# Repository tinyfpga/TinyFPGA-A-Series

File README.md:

# TinyFPGA-A-Series
The TinyFPGA A-Series boards are tiny bare-bones FPGA boards with a low cost per logic element.  They are programmed via their built-in JTAG interface and only contain the bare-minimum of components for the FPGA to function.  They measure 18mm x 30.5mm and fit well in breadboards.

## Features
The A-series boards use either XO2-256 or XO2-1200 FPGAs from Lattice.  It's a good idea to reference the [MachXO2 Family Data Sheet](http://www.latticesemi.com/~/media/LatticeSemi/Documents/DataSheets/MachXO23/MachXO2FamilyDataSheet.pdf?document_id=38834) for details.

### FPGA Feature Summary
|                  | TinyFPGA A1 | TinyFPGA A2 |
|------------------|:-----------:|:-----------:|
| FPGA Chip        |   XO2-256   |   XO2-1200  |
| Logic Cells      |     256     |     1200    |
| Distributed RAM  |   2 KBits   |   10 KBit   | 
| Block RAM        |             |   64 KBit   |
| User Flash       |             |   64 KBit   |
| Phase Lock Loops |             |      1      |
| User IO Pins     |     21      |     21      |

### Common Features
+ Small form-factor that is breadboard friendly; plenty of space on either side for connecting jumpers or components.
+ Easily accessible JTAG interface pins located both on the side IO connectors as well as a header on the top of the board.  This is an inexpensive way to support in circuit programming and testing.
+ Low-power and low-cost design relies on integrated FPGA functionality: internal configuration flash memory, internal clock generator, and fixed 3.3v power supply requirement.  External memory, clocks, and power supplies can be added external to the board.

## Building your own TinyFPGA A1 or A2 Boards
The TinyFPGA A-Series boards are possible to build in an adequately equipped home lab.  The resistors and capacitors are 0603 surface mount parts, and the FPGA is in a QFN32 package which can be soldered either by hand or with solder paste and a reflow oven.  It can be tricky to solder the QFN32 package by hand, but it is possible.  However it is much easier to use solder paste and a stencil along with a hot air-gun or reflow oven.  The following parts, supplies, and tools will help ensure a successful build:
+ Parts for the TinyFPGA [A1](https://octopart.com/bom-tool/Xj5vAWfE) or [A2](https://octopart.com/bom-tool/Cm0HpT6j)
+ [Lead-Free Solder Paste](https://www.amazon.com/gp/product/B00HKK6XHC)
+ [Stainless Steel Solder Paste Squeegee](http://dirtypcbs.com/store/details/14/solder-paste-squeegee)
+ [TinyFPGA A-Series Solder Paste Stencil](https://www.oshstencils.com)
  + You'll need to generate the gerber files and upload the solder paste layer.  Either stainless steel or polymide stencils should work.
+ [TinyFPGA A-Series PCBs](https://oshpark.com/shared_projects/2xu90fiY)
+ [Precision Tweezers](https://www.amazon.com/Precision-Anti-static-Marrywindix-Electronics-Jewelry-making/dp/B00DVIEJ14) for placing parts on the board
+ [Reflow Oven](http://www.whizoo.com/) or an [electric griddle](https://www.amazon.com/Presto-07211-Liddle-Griddle/dp/B00006IUWL)

## Buy TinyFPGA A1 or A2 Boards
If you don't want to go through the hassle of ordering parts, tools, and supplies and assembling the boards yourself you can order professionally assembled and tested boards from the [TinyFPGA Store](https://www.tindie.com/stores/tinyfpga/).  These boards are fabricated and assembled in a professional PCB fab that manufactures and assembles many other consumer, industrial and military electronics.  They go through an automated testing and programming process to ensure the board is healthy and ready to program over JTAG.

## Project Directory Structure
### board
This contains a [KiCad](http://kicad.org/) project with the schematic and layout of the B-series boards.  The board is designed with 4/4mil track size/spacing and 0.2mm hole size.

## License
The TinyFPGA A-Series project is an open source project licensed under GPLv3.  Please see the included LICENSE file for details.  If you do wish to distribute boards derived from this open source hardware project then you must also release the source files for the boards under GPLv3.  You are free to do this, but please improve upon the original design and provide a tangible benefit for users of the board.

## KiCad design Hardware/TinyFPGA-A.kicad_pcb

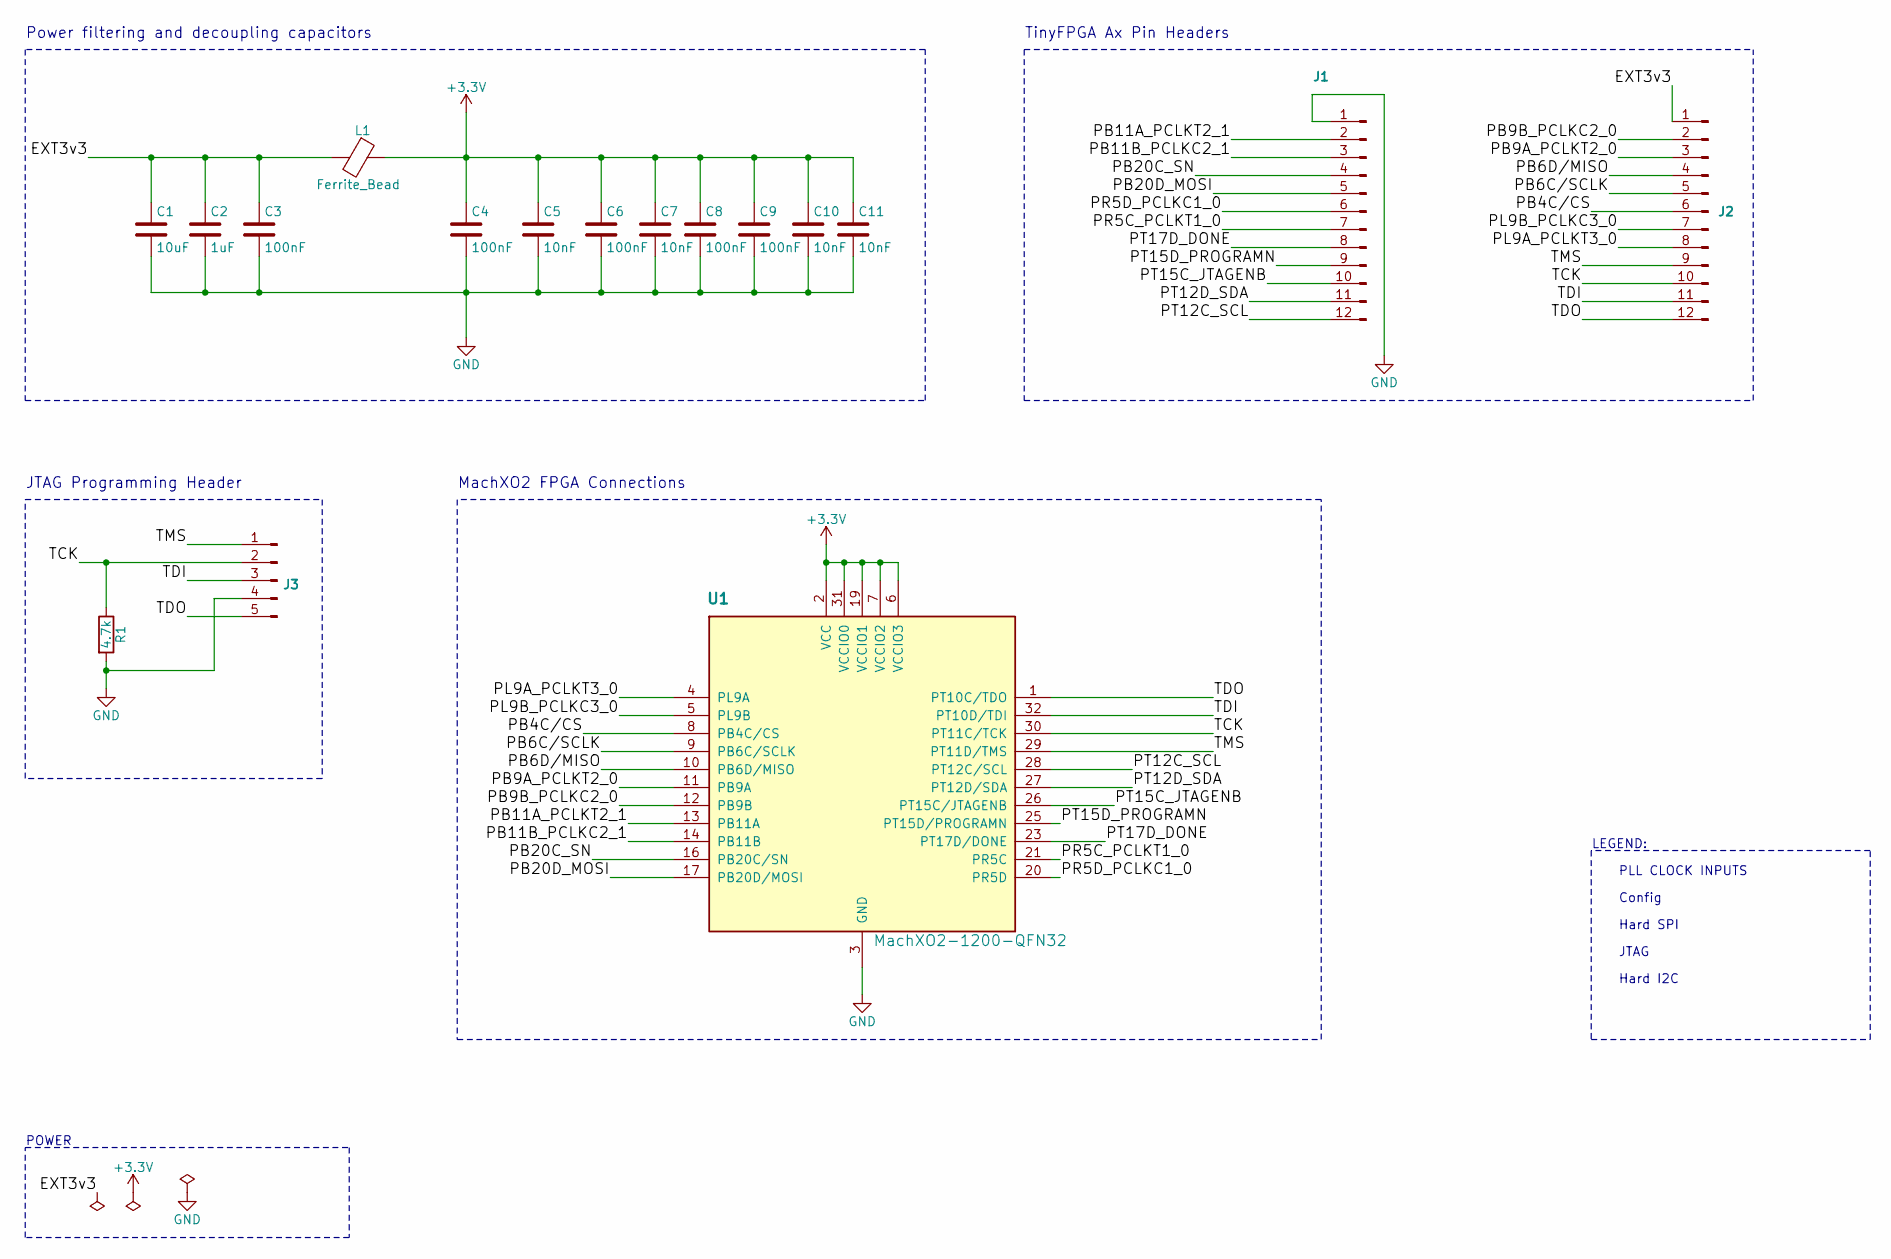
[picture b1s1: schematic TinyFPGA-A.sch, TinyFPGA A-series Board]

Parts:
C1: 10uF; C_0603
C2: 1uF; C_0603
C3, C4, C6, C8, C9: 100nF; C_0603
C5, C7, C10, C11: 10nF; C_0603
J1: Conn_01x12_Male; Pin_Header_Straight_1x12_Pitch2.54mm
J2: Conn_01x12_Male; Pin_Header_Straight_pin1round_1x12_Pitch2.54mm
J3: Conn_01x05_Male; Pin_Header_Straight_1x05_Pitch2.54mm
L1: Ferrite_Bead; L_0603
R1: 4.7k; R_0603
U1: MachXO2-1200-QFN32; 32QFN; Voltage - Supply 2.375V to 3.465V; MPN LCMXO2-1200HC-6SG32I

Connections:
+3V3: C4.1, C5.1, C6.1, C7.1, C8.1, C9.1, C10.1, C11.1, L1.1, U1.2 (VCC), U1.6 (VCCIO3), U1.7 (VCCIO2), U1.15 (VCCIO2), U1.18 (VCC), U1.19 (VCCIO1), U1.24 (VCCIO0), U1.31 (VCCIO0)
/EXT3v3: C1.1, C2.1, C3.1, J2.1, L1.2
/PB4C/CS: J2.6, U1.8 (PB4C/CS)
/PB6C/SCLK: J2.5, U1.9 (PB6C/SCLK)
/PB6D/MISO: J2.4, U1.10 (PB6D/MISO)
/PB9A_PCLKT2_0: J2.3, U1.11 (PB9A)
/PB9B_PCLKC2_0: J2.2, U1.12 (PB9B)
/PB11A_PCLKT2_1: J1.2, U1.13 (PB11A)
/PB11B_PCLKC2_1: J1.3, U1.14 (PB11B)
/PB20C_SN: J1.4, U1.16 (PB20C/SN)
/PB20D_MOSI: J1.5, U1.17 (PB20D/MOSI)
/PL9A_PCLKT3_0: J2.8, U1.4 (PL9A)
/PL9B_PCLKC3_0: J2.7, U1.5 (PL9B)
/PR5C_PCLKT1_0: J1.7, U1.21 (PR5C)
/PR5D_PCLKC1_0: J1.6, U1.20 (PR5D)
/PT12C_SCL: J1.12, U1.28 (PT12C/SCL)
/PT12D_SDA: J1.11, U1.27 (PT12D/SDA)
/PT15C_JTAGENB: J1.10, U1.26 (PT15C/JTAGENB)
/PT15D_PROGRAMN: J1.9, U1.25 (PT15D/PROGRAMN)
/PT17D_DONE: J1.8, U1.23 (PT17D/DONE)
/TCK: J2.10, J3.2, R1.1, U1.30 (PT11C/TCK)
/TDI: J2.11, J3.3, U1.32 (PT10D/TDI)
/TDO: J2.12, J3.5, U1.1 (PT10C/TDO)
/TMS: J2.9, J3.1, U1.29 (PT11D/TMS)
GND: C1.2, C2.2, C3.2, C4.2, C5.2, C6.2, C7.2, C8.2, C9.2, C10.2, C11.2, J1.1, J3.4, R1.2, U1.3 (GND), U1.22 (GND), U1.33 (GND)

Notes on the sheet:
JTAG Programming Header
MachXO2 FPGA Connections
Power filtering and decoupling capacitors
TinyFPGA Ax Pin Headers
POWER
LEGEND:
PLL CLOCK INPUTS
Config
Hard SPI
JTAG
Hard I2C

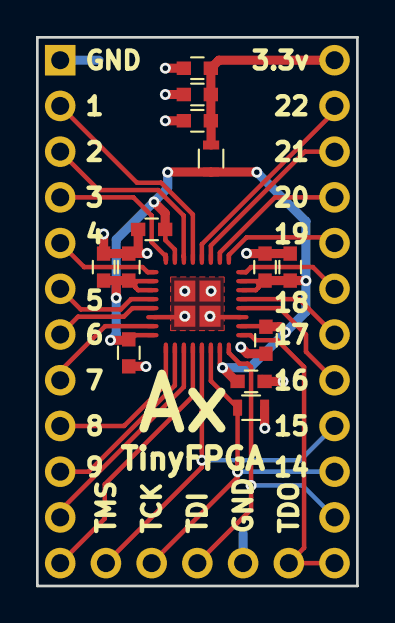
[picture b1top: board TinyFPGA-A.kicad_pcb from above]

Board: 2 copper layers, 17.8 x 30.5 mm, 17 parts (0 on the bottom side), 25 nets.

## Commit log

2017-07-09 ignore kicad backup files, vim files, etc...
2017-07-09 added KiCad design files
2017-07-16 Update README.md
    correct RAM amounts
2017-07-20 added template projects for A1 and A2
2017-10-07 made schematic pretty, added pdf
2020-02-15 adding TinyFPGA AX reference cards
2021-07-11 Updated schematic for Kicad v.5.1.9-1
2021-07-11 Time to push it.
2021-07-11 added gerber-folder
2021-11-10 Update README.md
    https://forum.kicad.info/t/warning-avoid-all-links-to-kicad-pcb-org-use-kicad-org/31521
